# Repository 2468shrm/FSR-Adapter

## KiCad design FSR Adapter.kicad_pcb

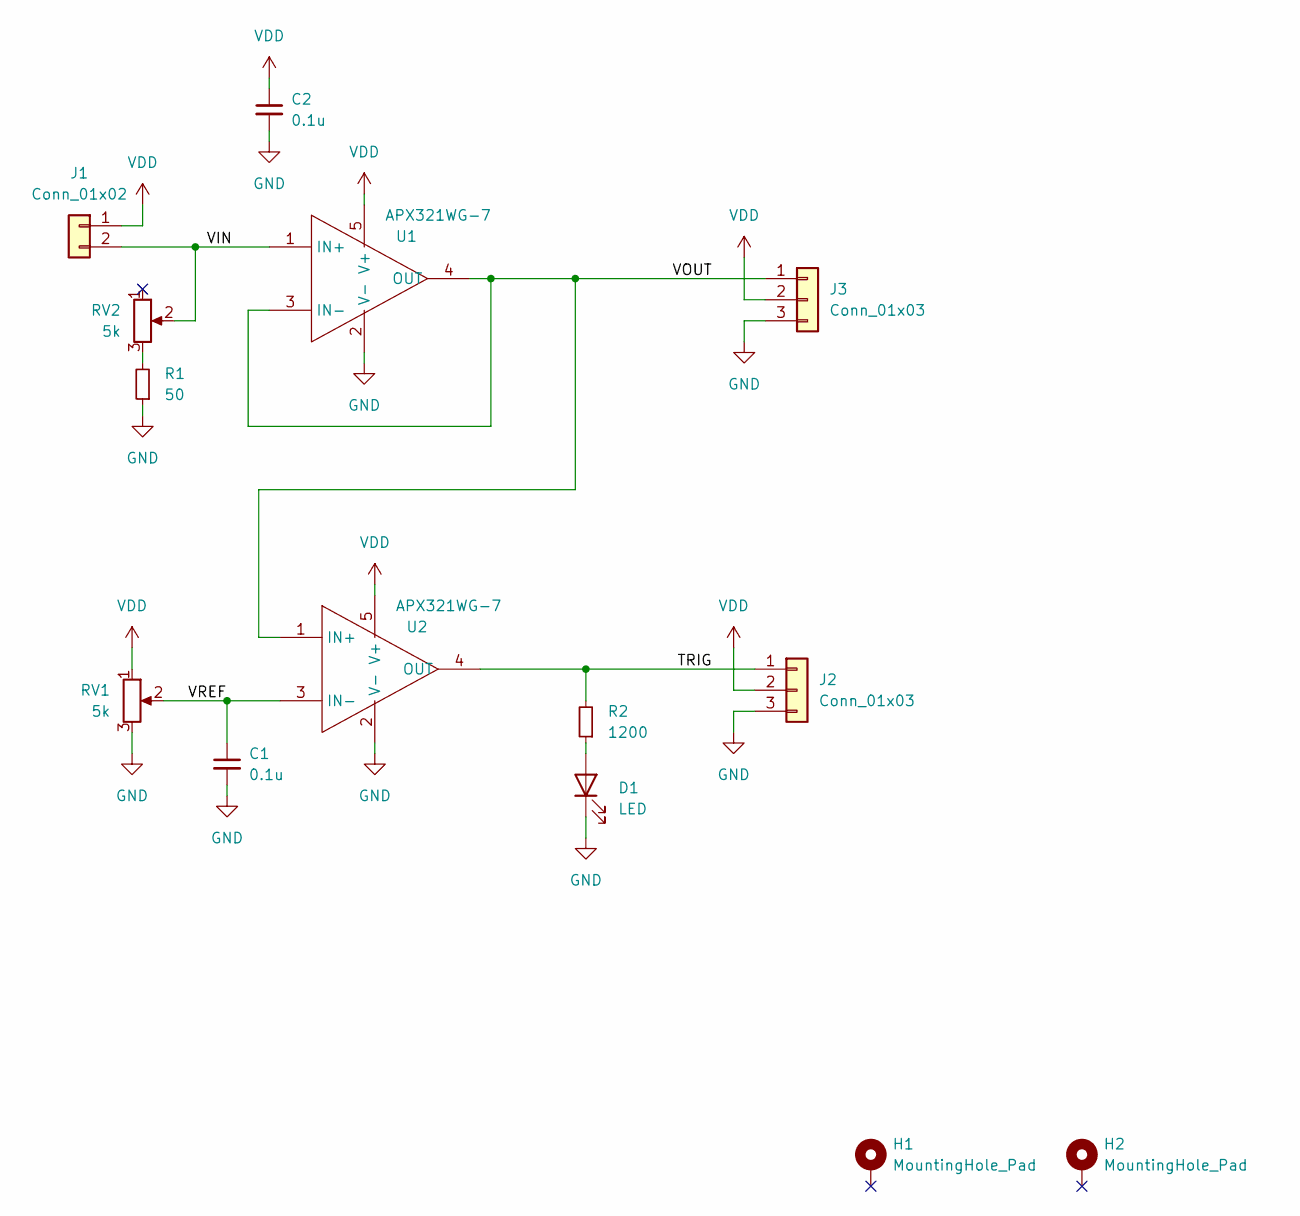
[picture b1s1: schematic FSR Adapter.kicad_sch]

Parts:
C1, C2: 0.1u; C_1206_3216Metric
D1: LED; LED_1206_3216Metric
H1, H2: MountingHole_Pad; MountingHole_2.2mm_M2_DIN965_Pad
J1: Conn_01x02; PinHeader_1x02_P2.54mm_Vertical
J2, J3: Conn_01x03; PinSocket_1x03_P2.54mm_Vertical
R1: 50; R_1206_3216Metric
R2: 1200; R_1206_3216Metric
RV1, RV2: 5k; 23AR5KLFTR
U1, U2: APX321WG-7; SOT95P285X145-5N; Manufacturer_Part_Number APX321WG-7; Mouser Part Number 621-APX321WG-7

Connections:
/TRIG: J2.1, R2.2, U2.4 (OUT)
/VIN: J1.2, RV2.2, U1.1 (IN+)
/VOUT: J3.1, U1.3 (IN-), U1.4 (OUT), U2.1 (IN+)
/VREF: C1.1, RV1.2, U2.3 (IN-)
GND: C1.2, C2.2, D1.1 (K), J2.3, J3.3, R1.1, RV1.3, U1.2 (V-), U2.2 (V-)
unnamed: D1.2 (A), R2.1
unnamed: R1.2, RV2.3
VDD: C2.1, J1.1, J2.2, J3.2, RV1.1, U1.5 (V+), U2.5 (V+)

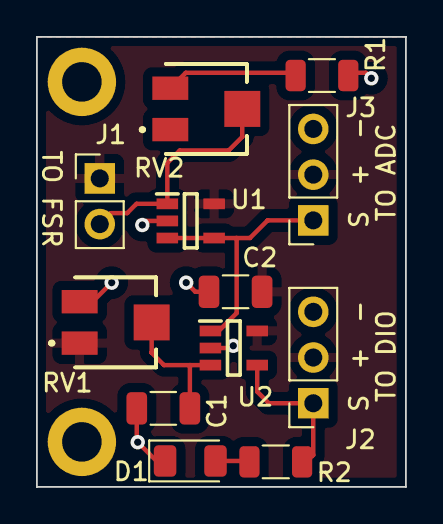
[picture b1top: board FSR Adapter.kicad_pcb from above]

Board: 2 copper layers, 20.5 x 25.0 mm, 14 parts (0 on the bottom side), 8 nets.

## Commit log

2024-01-05 added PCB files
2024-01-05 adding manufacturing files (Gerbers)
2024-01-05 added 3D file from KiCAD (step)
2024-01-05 adding images for docs
2024-01-05 adding CAD files for 3D printed enclosure

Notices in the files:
FSR Adapter.kicad_pcb:
(c) 2023 SHRM
